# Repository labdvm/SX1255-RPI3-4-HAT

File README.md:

[![CC BY-NC-SA 4.0][cc-by-nc-sa-shield]][cc-by-nc-sa]

# SX1255_HAT-hw (schematic and pcb modified by Z32IT)
Raspberry Pi 3-4 shield with the SX1255 RF transceiver chip.

## Usage
### RPi sample config code
Sample Raspberry Pi code for SX1255 control can be found [here](https://gist.github.com/sp5wwp/25fa989ebd98b3b707eadae9b63af679).<br>
[I2S slave overlay](https://github.com/AkiyukiOkayasu/RaspberryPi_I2S_Slave) is required. Sample rate for both RX and TX is 125kHz.

RX/TX frequency setting:
```
./sx1255-spi 435000000 438000000
```

### Example RX with ZeroMQ
```
arecord -t raw -f S32_LE -r 192000 -c 2 --device="hw:0,1" | ./int_to_short | ./zmq-pub
```

In which `int_to_short` is a simple `int` to `short` format converter:
```C
while(1)
{
  ioctl(STDIN_FILENO, FIONREAD, &rcvd);
  if(rcvd>0)
  {
    if(read(STDIN_FILENO, inp, rcvd)==rcvd)
    {
      for(int i=0; i<rcvd; i+=8)
      {
        memcpy(&out[i/2  ], &inp[i  +2], 2);
        memcpy(&out[i/2+2], &inp[i+4+2], 2);
      }

      write(STDOUT_FILENO, out, rcvd/2);
    }
  }
}
```

### Example TX with ZeroMQ
```
./zmq-sub 192.168.50.243:17018 | aplay -t raw -f S32_LE -r 192000 -c 2 --device="hw:0,0"
```

## License
This work is licensed under a
[Creative Commons Attribution-NonCommercial-ShareAlike 4.0 International License][cc-by-nc-sa].

[![CC BY-NC-SA 4.0][cc-by-nc-sa-image]][cc-by-nc-sa]

[cc-by-nc-sa]: http://creativecommons.org/licenses/by-nc-sa/4.0/
[cc-by-nc-sa-image]: https://licensebuttons.net/l/by-nc-sa/4.0/88x31.png
[cc-by-nc-sa-shield]: https://img.shields.io/badge/License-CC%20BY--NC--SA%204.0-lightgrey.svg

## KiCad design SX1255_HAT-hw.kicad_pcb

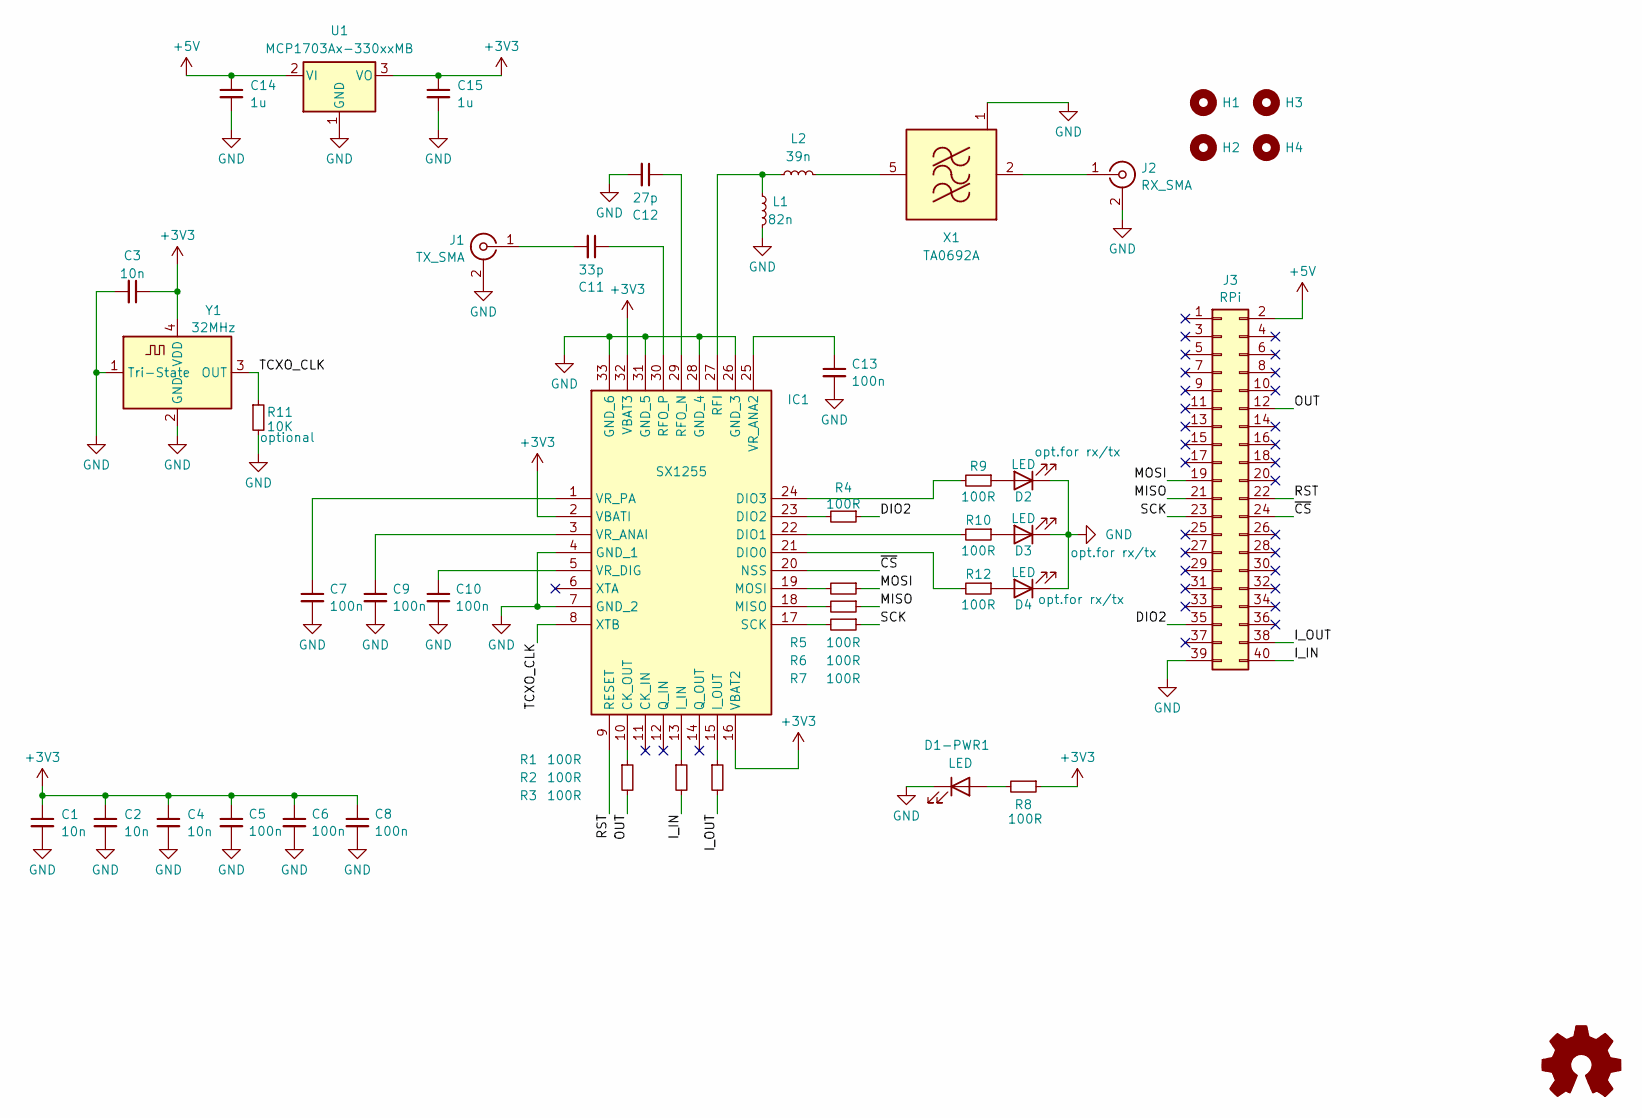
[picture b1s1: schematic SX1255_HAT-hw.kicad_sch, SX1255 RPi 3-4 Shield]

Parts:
C1, C2, C3, C4: 10n; C_0805_2012Metric; MPN C0603C103M4REC7411
C5, C6, C7, C8, C9, C10, C13: 100n; C_0805_2012Metric; MPN 06035G104ZAT2A
C11: 33p; C_0805_2012Metric; MPN VJ0603A330KXAPW1BC
C12: 27p; C_0805_2012Metric; MPN AC0603JRNPO9BN270
C14, C15: 1u; C_0805_2012Metric; MPN C0603C103M4REC7411
D1-PWR1, D2, D3, D4: LED; LED_0805_2012Metric
H1, H2, H3, H4: MountingHole; MountingHole_2.7mm_M2.5_DIN965
IC1: SX1255; QFN50P500X500X80-33N-D; MPN SX1255IWLTRT
J1: TX_SMA; SMA_Amphenol_901-144_Vertical; MPN RF2-04A-T-00-50-G
J2: RX_SMA; SMA_Amphenol_901-144_Vertical; MPN RF2-04A-T-00-50-G
J3: RPi; PinSocket_2x20_P2.54mm_Vertical
L1: 82n; L_0805_2012Metric; MPN AISC-0603-R082J-T
L2: 39n; L_0805_2012Metric; MPN AISC-0603-R039J-T
R1, R2, R3, R4, R5, R6, R7, R8, R9, R10, R12: 100R; R_0805_2012Metric; MPN CRCW0603100RFKECC
R11: 10K; R_0805_2012Metric; MPN CRCW0603100RFKECC
SYM1: Logo_Open_Hardware_Small; OSHW-Logo2_7.3x6mm_SilkScreen
U1: MCP1703Ax-330xxMB; SOT-89-3
X1: TA0692A; Filter_SAW-6_3.8x3.8mm
Y1: 32MHz; Crystal_SMD_3225-4Pin_3.2x2.5mm; MPN ECS-TXO-20CSMV4-320-AY-TR

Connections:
+3V3: C1.1, C2.1, C3.1, C4.1, C5.1, C6.1, C8.1, C15.1, IC1.2 (VBATI), IC1.16 (VBAT2), IC1.32 (VBAT3), R8.1, U1.3 (VO), Y1.4 (VDD)
+5V: C14.1, J3.2, U1.2 (VI)
/DIO2: J3.35, R4.1
/I_IN: J3.40, R2.2
/I_OUT: J3.38, R3.2
/MISO: J3.21, R6.1
/MOSI: J3.19, R5.1
/OUT: J3.12, R1.2
/RST: IC1.9 (RESET), J3.22
/SCK: J3.23, R7.1
/TCXO_CLK: IC1.8 (XTB), R11.1, Y1.3 (OUT)
/~CS: IC1.20 (NSS), J3.24
GND: C1.2, C2.2, C3.2, C4.2, C5.2, C6.2, C7.2, C8.2, C9.2, C10.2, C12.2, C13.2, C14.2, C15.2, D1-PWR1.1 (K), D2.1 (K), D3.1 (K), D4.1 (K), IC1.4 (GND_1), IC1.7 (GND_2), IC1.26 (GND_3), IC1.28 (GND_4), IC1.31 (GND_5), IC1.33 (GND_6), J1.2 (Ext), J2.2 (Ext), J3.39, L1.1, R11.2, U1.1 (GND), X1.1 (GND), X1.3 (GND), X1.4 (GND), X1.6 (GND), Y1.1 (Tri-State), Y1.2 (GND); also elsewhere on the board
unnamed 13: D1-PWR1.2 (A), R8.2; also elsewhere on the board
unnamed: D2.2 (A), R9.1
unnamed: D3.2 (A), R10.1
unnamed: D4.2 (A), R12.1
unnamed: IC1.10 (CK_OUT), R1.1
unnamed: IC1.21 (DIO0), R12.2
unnamed: IC1.22 (DIO1), R10.2
unnamed: IC1.23 (DIO2), R4.2
unnamed: IC1.24 (DIO3), R9.2
unnamed: IC1.13 (I_IN), R2.1
unnamed: IC1.15 (I_OUT), R3.1
unnamed: IC1.18 (MISO), R6.2
unnamed: IC1.19 (MOSI), R5.2
unnamed: IC1.27 (RFI), L1.2, L2.2
unnamed: C12.1, IC1.29 (RFO_N)
unnamed: C11.1, IC1.30 (RFO_P)
unnamed: IC1.17 (SCK), R7.2
unnamed: C13.1, IC1.25 (VR_ANA2)
unnamed: C9.1, IC1.3 (VR_ANAI)
unnamed: C10.1, IC1.5 (VR_DIG)
unnamed: C7.1, IC1.1 (VR_PA)
unnamed: C11.2, J1.1 (In)
unnamed: J2.1 (In), X1.2 (IN)
unnamed: L2.1, X1.5 (OUT)

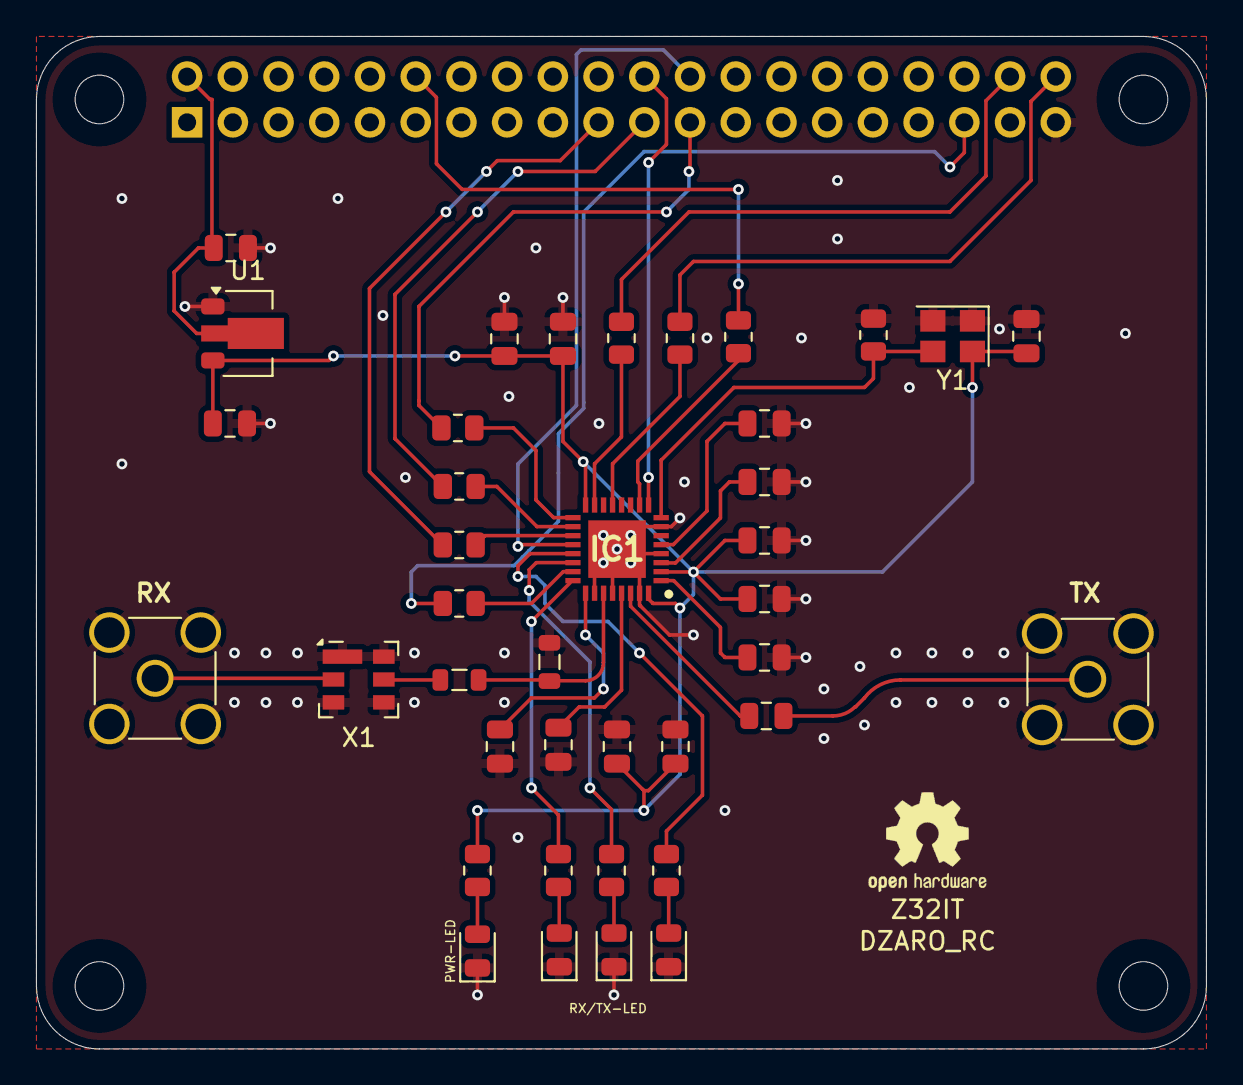
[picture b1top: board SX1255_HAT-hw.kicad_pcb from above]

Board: 2 copper layers, 65.0 x 56.2 mm, 45 parts (1 on the bottom side), 37 nets.

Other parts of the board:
D1-PWR: LED; LED_0805_2012Metric

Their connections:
GND: D1-PWR.1 (K); also elsewhere on the board
unnamed 13: D1-PWR.2 (A); also elsewhere on the board
